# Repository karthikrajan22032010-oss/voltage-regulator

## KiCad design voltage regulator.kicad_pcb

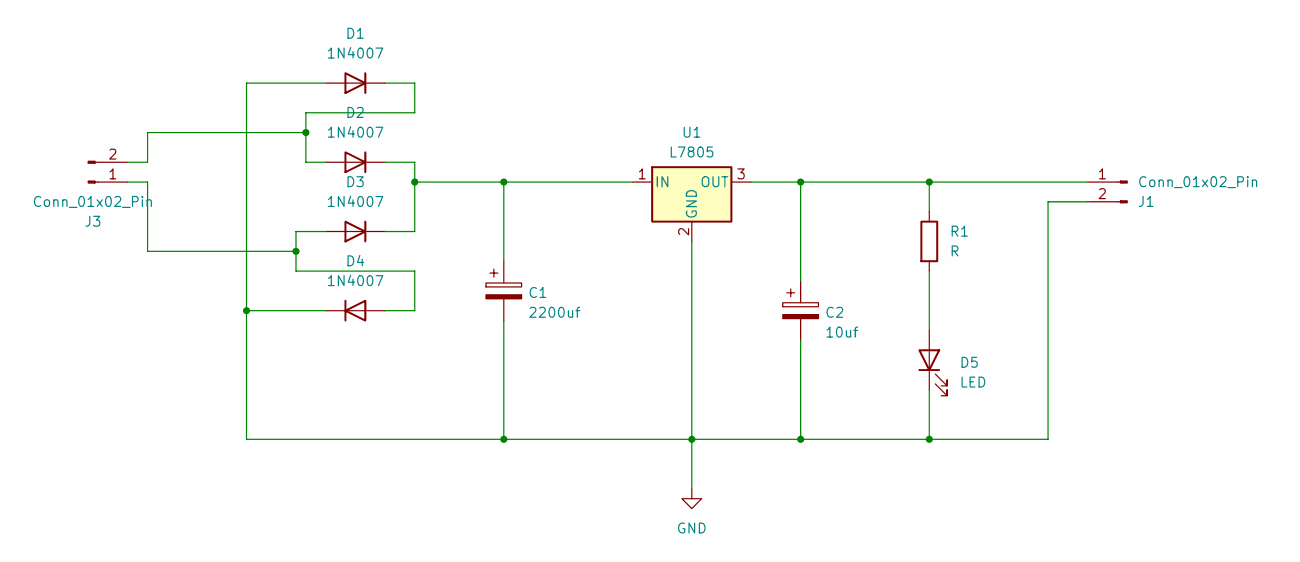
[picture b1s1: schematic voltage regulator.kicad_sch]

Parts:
C1: 2200uf; CP_Radial_D8.0mm_P5.00mm
C2: 10uf; CP_Radial_D4.0mm_P2.00mm
D1, D2, D3, D4: 1N4007; D_DO-41_SOD81_P10.16mm_Horizontal
D5: LED; LED_D3.0mm
J1, J3: Conn_01x02_Pin; PinHeader_1x02_P1.27mm_Vertical
R1: R; R_Axial_DIN0204_L3.6mm_D1.6mm_P5.08mm_Horizontal
U1: L7805; TO-220-3_Horizontal_TabDown

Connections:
GND: C1.2, C2.2, D1.2 (A), D4.1 (K), D5.1 (K), J1.2, U1.2 (GND)
unnamed: D1.1 (K), D2.2 (A), J3.2
unnamed: C1.1, D2.1 (K), D3.1 (K), U1.1 (IN)
unnamed: D3.2 (A), D4.2 (A), J3.1
unnamed: D5.2 (A), R1.2
unnamed: C2.1, J1.1, R1.1, U1.3 (OUT)

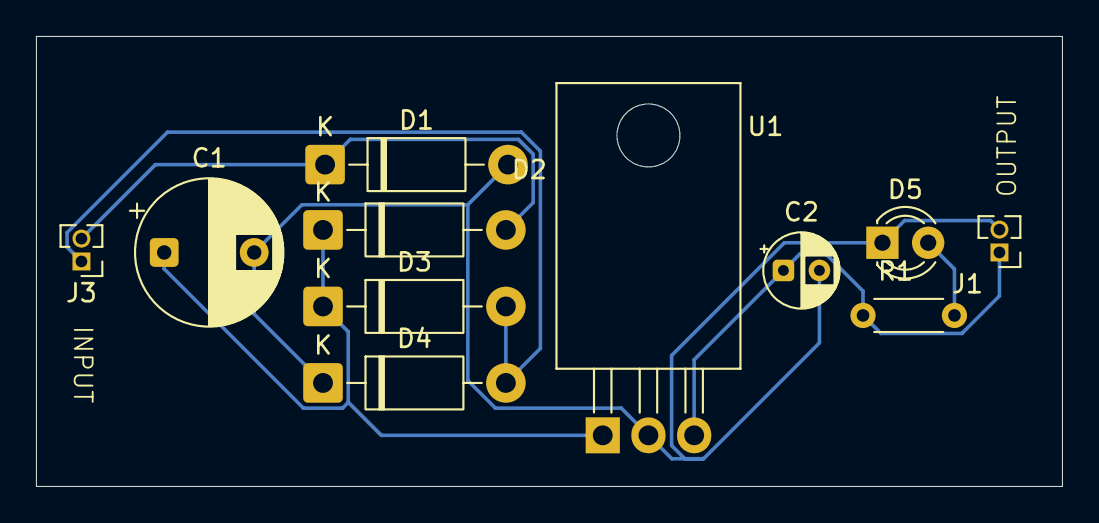
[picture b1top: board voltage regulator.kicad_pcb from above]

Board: 2 copper layers, 57.0 x 25.0 mm, 11 parts (0 on the bottom side), 6 nets.
